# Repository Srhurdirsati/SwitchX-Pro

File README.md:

# SwitchX-Pro

SwitchX Pro is a 6-channel WiFi smart switch system with real-time clock automation, allowing precise control of home appliances anytime, anywhere.

## Working

1 - *Put the ESP32 in boot mode and connect it to your PCB*

2 - *Use arduino IDE to upload the CODE to the Board and* **make sure that you have entered correct SSID and it's password in the code** . *The following libraries should downloaded and transferred in the microcontroller :*

`<WiFi.h>`

`<WebServer.h>`

`<EEPROM.h>`

`<Wire.h>`

`"RTClib.h"`

`"time.h"`

**Now SwitchX-Pro will be ready to function .**

3 - *Connect the  main AC phase wire to AC slot and the 6 Appliances or switches wire ( That are needed to be operated with this PCB ) to the OUT 1-6 slots .*

4 - *Now the PCB is completely set up and would function great if everything goes as expected* :) 

5 - *Find your ESP-32 ip address by Arduino IDE serial monitor* .

6 - *Open browser on any device that is connected to same Wi-Fi and put the ip address that you found out from serial monitor from IDE* .

All set , you are now connected to SwitchX-Pro and can operate it and perform all the present functions.

### Features

> Set on and off time for each relay respectively.

> Configure onboard time.

> Toggle each relay manually.

## Images

## JLCPCB

` Project Total = 120 USD `

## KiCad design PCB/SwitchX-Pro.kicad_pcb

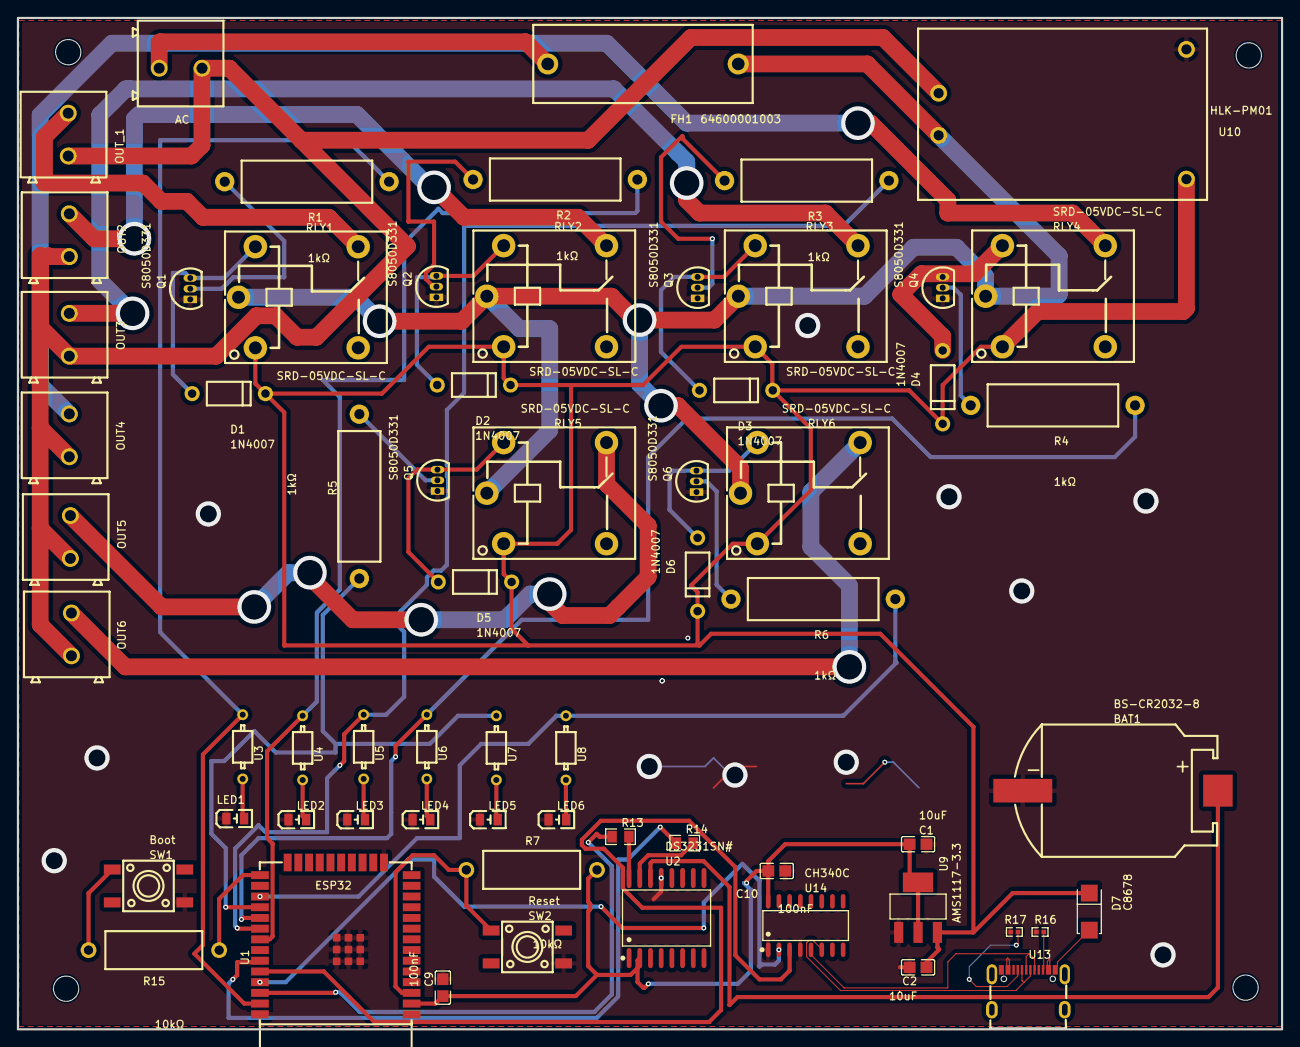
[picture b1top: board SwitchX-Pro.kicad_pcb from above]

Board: 2 copper layers, 150.0 x 120.0 mm, 68 parts (0 on the bottom side), 51 nets.

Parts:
AC: WJ500V-5.08-2P-14-00A; CONN-TH_2P-P5.00_WJ500V-5.08-2P
BAT1: BS-CR2032-8; BAT-SMD_BS-CR2032-8
C1, C2: 10uF; C0805
C9, C10: 100nF; C0805
D1, D2, D3, D4, D5, D6: 1N4007; DO-41_BD2.4-L4.7-P8.70-D0.9-RD
D7: C8678; SMA_L4.3-W2.6-LS5.2-RD
FH1: 64600001003
Hole_gge9527: Hole_gge9527
Hole_gge9566: Hole_gge9566
Hole_gge9581: Hole_gge9581
Hole_gge9596: Hole_gge9596
LED1, LED2, LED3, LED4, LED5, LED6: YLED0805R; LED0805-R-RD_RED
OUT2, OUT3, OUT4, OUT5, OUT6: WJ500V-5.08-2P-14-00A; CONN-TH_2P-P5.00_WJ500V-5.08-2P
OUT_1: WJ500V-5.08-2P-14-00A; CONN-TH_2P-P5.00_WJ500V-5.08-2P
Q1, Q2, Q3, Q4, Q5, Q6: S8050D331; TO-92-3_L5.1-W4.1-P1.27-L
R1, R2, R3, R4, R5, R6: 1kΩ; RES-TH_BD5.0-L15.5-P19.50-D0.7
R7, R15: 10kΩ; RES-TH_BD4.5-L11.5-P15.50-D0.7
R13, R14: 4.7kΩ; R0805
R16, R17: 5.1kΩ; R0402
RLY1, RLY2, RLY3, RLY4, RLY5, RLY6: SRD-05VDC-SL-C; RELAY-TH_SRD-XXVDC-XL-C
SW1: Boot; KEY-SMD_4P-L6.0-W6.0-P3.90-LS9.0
SW2: Reset; KEY-SMD_4P-L6.0-W6.0-P3.90-LS9.0
U1: ESP32; WIFI-SMD_ESP32-WROOM-32E
U2: DS3231SN#; SOIC-16_L10.3-W7.5-P1.27-LS10.3-BL
U3, U4, U5, U6, U7, U8: 220Ω; RES-TH_BD2.3-L3.7-P7.70-D0.9
U9: AMS1117-3.3; SOT-223-3_L6.5-W3.4-P2.30-LS7.0-BR
U10: HLK-PM01; PWRM-TH_HLK-PM01
U13: TYPEC-700-ARP16X7; TYPE-C-SMD_TYPEC16PL7.35MM
U14: CH340C; SOP-16_L10.0-W3.9-P1.27-LS6.0-BL

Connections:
3.3V: C1.1, C9.1, C10.2, R7.1, U1.2, U2.2, U9.2, U9.4, U14.16
5V: C2.1, D1.1, D2.1, D3.1, D4.1, D5.1, D6.1, D7.1, RLY1.1, RLY2.1, RLY3.1, RLY4.1, RLY5.1, RLY6.1, U9.3, U10.4
AC_MAIN: AC.1, FH1.1
BOOT: R15.1, U1.25
D+: U13.A6, U13.B6, U14.5
D-: U13.A7, U13.B7, U14.6
EN: R7.2, SW2.1, U1.3
GND: BAT1.1, C1.2, C2.2, C9.2, C10.1, LED1.2, LED2.2, LED3.2, LED4.2, LED5.2, LED6.2, Q1.1, Q2.1, Q3.1, Q4.1, Q5.1, Q6.1, R16.1, R17.1, SW1.4, SW2.4, U1.1, U1.15, U1.38, U1.39, U2.13, U9.1, U10.3, U13.A4, U13.A9, U13.B4, U13.B9, U14.1, U14.4
LED1_1: LED1.1, U3.2
LED2_1: LED2.1, U4.2
LED3_1: LED3.1, U5.2
LED4_1: LED4.1, U6.2
LED5_1: LED5.1, U7.2
LED6_1: LED6.1, U8.2
LIVE: FH1.2, RLY1.5, RLY2.5, RLY3.5, RLY4.5, RLY5.5, RLY6.5, U10.2
LIVE_1: OUT_1.2, RLY1.3
LIVE_2: OUT2.2, RLY2.3
LIVE_3: OUT3.2, RLY3.3
LIVE_4: OUT4.2, RLY4.3
LIVE_5: OUT5.2, RLY5.3
LIVE_6: OUT6.2, RLY6.3
NEUTRAL: AC.2, OUT2.1, OUT3.1, OUT4.1, OUT5.1, OUT6.1, OUT_1.1, U10.1
Q1_2: Q1.2, R1.2
Q2_2: Q2.2, R2.2
Q3_2: Q3.2, R3.2
Q4_2: Q4.2, R4.2
Q5_2: Q5.2, R5.2
Q6_2: Q6.2, R6.2
RELAY_1: R1.1, U1.37, U3.1
RELAY_2: R2.1, U1.31, U4.1
RELAY_3: R3.1, U1.30, U5.1
RELAY_4: R4.1, U1.29, U6.1
RELAY_5: R5.1, U1.28, U7.1
RELAY_6: R6.1, U1.27, U8.1
RLY1_4: D1.2, Q1.3, RLY1.4
RLY2_4: D2.2, Q2.3, RLY2.4
RLY3_4: D3.2, Q3.3, RLY3.4
RLY4_4: D4.2, Q4.3, RLY4.4
RLY5_4: D5.2, Q5.3, RLY5.4
RLY6_4: D6.2, Q6.3, RLY6.4
RXD: U1.34, U14.3
SCL: R13.1, U1.36
SDA: R14.1, U1.33
SW1_1: R15.2, SW1.1
TXD: U1.35, U14.2
U2_15: R14.2, U2.15
U2_16: R13.2, U2.16
U13_A5: R17.2, U13.A5
U13_B5: R16.2, U13.B5
U13_B12: D7.2, U13.A12, U13.B12
VBAT: BAT1.2, U2.14
